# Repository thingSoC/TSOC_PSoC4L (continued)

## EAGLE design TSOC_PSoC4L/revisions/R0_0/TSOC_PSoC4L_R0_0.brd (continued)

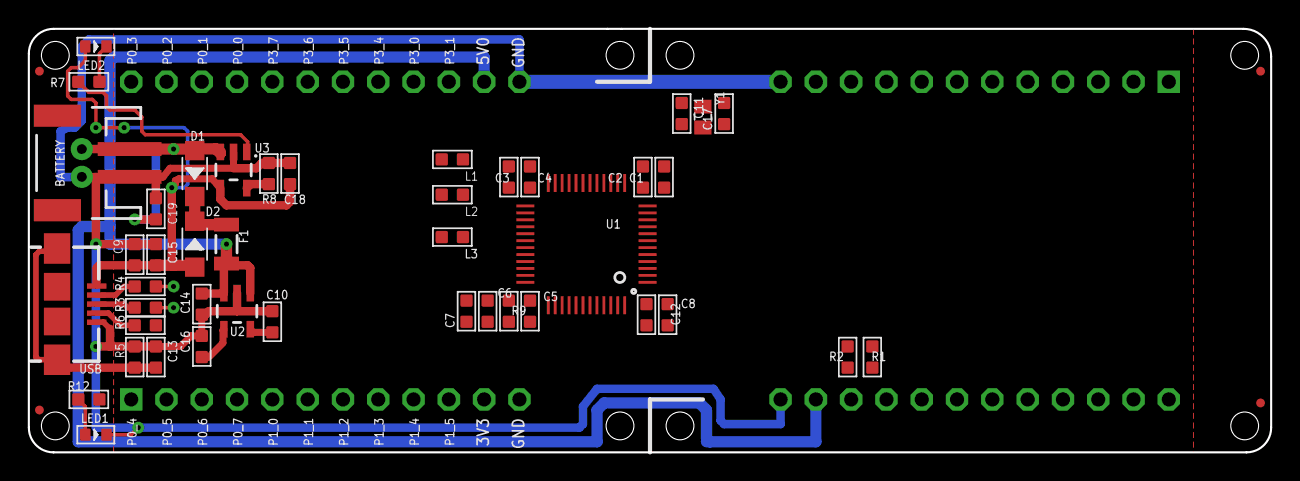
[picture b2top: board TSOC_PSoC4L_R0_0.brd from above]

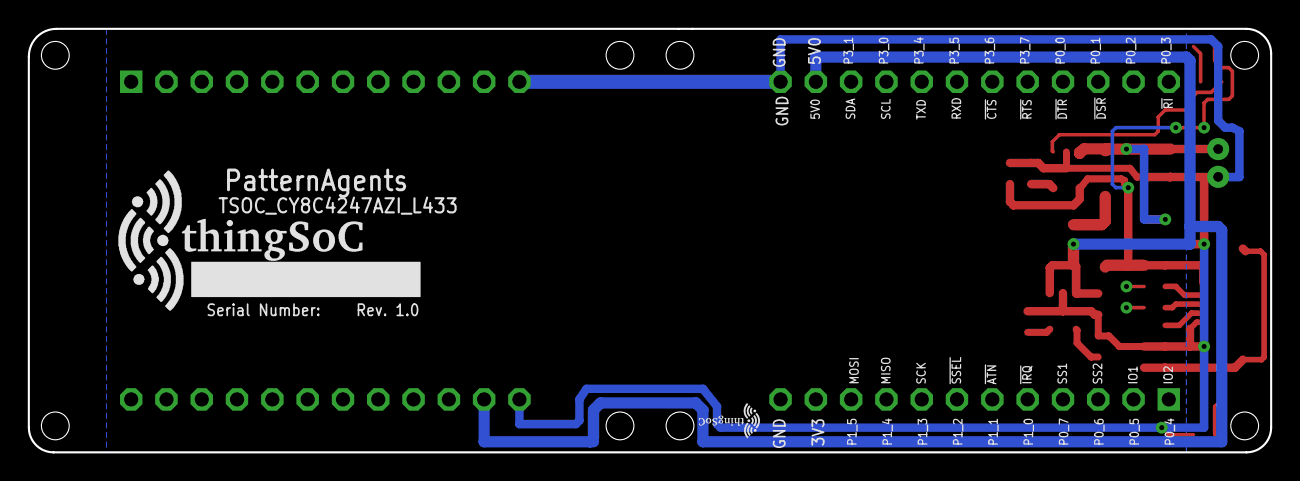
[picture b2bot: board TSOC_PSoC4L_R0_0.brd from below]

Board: 2 copper layers, 89.4 x 30.5 mm, 53 parts (3 on the bottom side), 44 nets.

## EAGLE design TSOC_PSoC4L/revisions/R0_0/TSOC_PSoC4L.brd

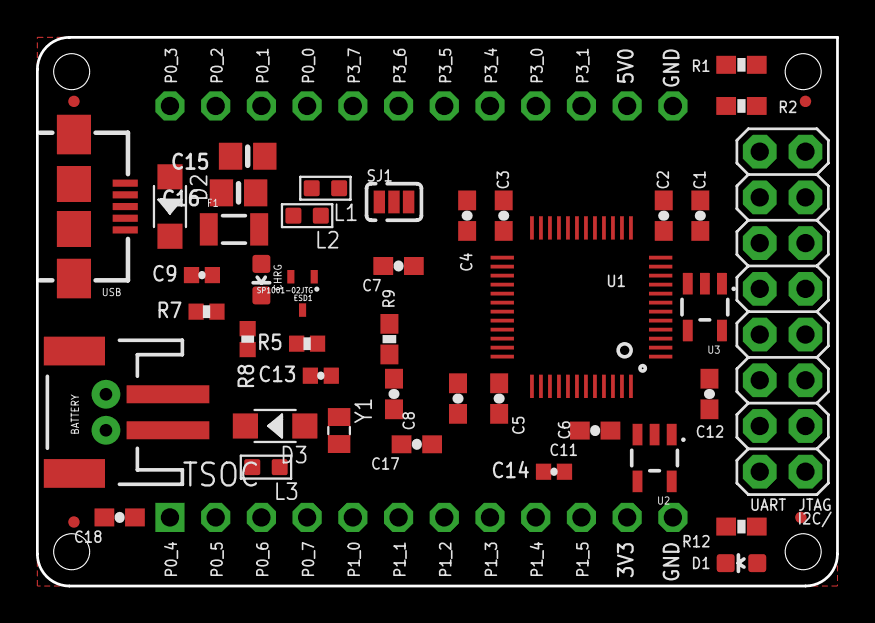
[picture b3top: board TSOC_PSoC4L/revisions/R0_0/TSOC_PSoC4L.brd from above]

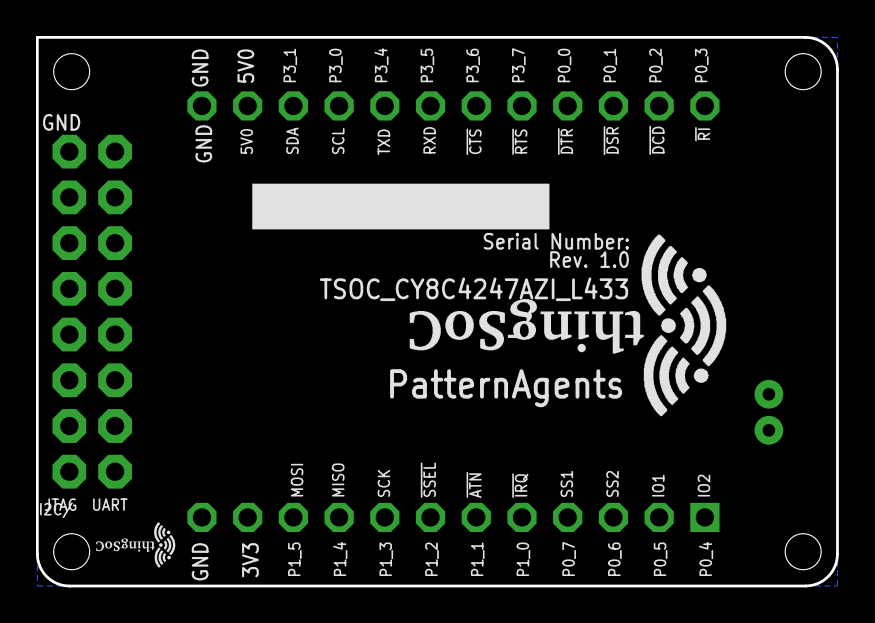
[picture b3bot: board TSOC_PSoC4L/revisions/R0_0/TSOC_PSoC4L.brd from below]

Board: 2 copper layers, 44.5 x 30.5 mm, 50 parts (3 on the bottom side), 51 nets, no tracks yet.

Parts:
BATTERY: JST-2-SMD
C1, C4, C5, C7: 0.1uF; 0603-CAP
C2, C3, C6, C8, C12, C18: 1uF; 0603-CAP
C9: 0.1uF; 0402-CAP
C11, C17: 12pF; 0603-CAP
C13, C14: 470nF; 0402-CAP
C15, C16: 10µF; 0805-NO
CHRG: RED; LED-0603
D1: LED-0603
D2, D3: 20V-1A; SOD-123
ESD1: SP1001-02JTG; SC70-3
F1: 500mA-PTC; PTC-1206
FID1, FID2, FID3, FID4: FIDUCIALUFIDUCIAL; MICRO-FIDUCIAL
J1: 2X8
J1P: JST-2-PTH-NS
L1, L2, L3: 330OHM-500MA; L0603
R1, R2: 2K2; 0603-RES
R5: 1M; 0402-RES
R7: 1K; 0402-RES
R8: 10K; 0402-RES
R9: 10K; 0603-RES
R12: 1K; 0603-RES
SJ1: JMP-3-NC
TSOC: TSOC-24-BB; TSOC-BB-S24
U1: CY8C4247AZI-L433; TQFP-7X7-48
U2: MIC5219 3.3V; SOT23-5
U3: MCP73831; SOT23-5
U$1: TSOC-PCB-SINGLE; TSOC-BB-BRD-DIM
U$100: TSOC-LOGO-SMALL; TSOC-LOGO-SML
U$101: TSOC-LOGO-LRG
USB: USB_AB; USB-AB-MICRO-SMD
Y1: 3.2768KHZ; X2-SMD-L2.0X1.2X0.55MM

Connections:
3V3: C15.1, SJ1.1, TSOC.11B, U2.5
5V0: C16.1, D2.-, D3.-, L2.1, L3.1, SJ1.3, TSOC.11C, U2.1, U2.3
!XRES: C7.1, J1.5, R9.1, U1.36
BYPASS1: C14.1, U2.4
CLED: CHRG.C, R7.2
CSTAT: R7.1, U3.1
GND: BATTERY.1, C1.2, C2.2, C3.2, C4.2, C5.2, C6.2, C7.2, C8.2, C9.2, C11.2, C12.2, C13.2, C14.2, C15.2, C16.2, C17.2, C18.2, D1.C, ESD1.3, J1.15, J1.16, J1P.2, R5.2, R8.1, TSOC.12B, TSOC.12C, U1.10, U1.38, U1.41, U2.2, U3.2, USB.GND
unnamed: R8.2, U3.5
unnamed: D1.A, R12.1
P0_0: TSOC.4C, U1.28
P0_1: TSOC.3C, U1.29
P0_2: TSOC.2C, U1.30
P0_3: TSOC.1C, U1.31
P0_4: C11.1, TSOC.1B, U1.32, Y1.1
P0_5: C17.1, TSOC.2B, U1.33, Y1.2
P0_6: TSOC.3B, U1.34
P0_7: TSOC.4B, U1.35
P1_0: TSOC.5B, U1.42
P1_1: TSOC.6B, U1.43
P1_2: TSOC.7B, U1.44
P1_3: TSOC.8B, U1.45
P1_4: TSOC.9B, U1.46
P1_5: TSOC.10B, U1.47
P1_6: R12.2, U1.48
P1_7: C12.1, U1.1
P2_0: J1.1, U1.2
P2_2: J1.2, U1.4
P2_3: J1.4, U1.5
P2_4: J1.6, U1.6
P2_7: J1.14, U1.9
P3_0: J1.3, R2.1, TSOC.9C, U1.12
P3_1: J1.13, R1.1, TSOC.10C, U1.13
P3_2: J1.9, U1.14
P3_3: J1.7, U1.16
P3_4: TSOC.8C, U1.17
P3_5: TSOC.7C, U1.18
P3_6: TSOC.6C, U1.19
P3_7: TSOC.5C, U1.20
P4_0: J1.10, U1.22
SJ1: L1.1, SJ1.2
USB1_DM: ESD1.2, U1.24, USB.D-
USB1_DP: ESD1.1, U1.23, USB.D+
USB1_SHIELD: C13.1, R5.1, USB.SHIELD1, USB.SHIELD2
USB1_VBUS: C18.1, CHRG.A, D2.+, F1.2, U1.25, U3.4
VBAT: BATTERY.2, D3.+, J1P.1, U3.3
VBUS1: C9.1, F1.1, USB.VBUS
VCC: J1.11, J1.12
VCCD: C8.1, U1.37
VDDA: C1.1, C2.1, L3.2, U1.40
VDDD: C5.1, C6.1, L2.2, R9.2, U1.39
VDDIO: C3.1, C4.1, L1.2, R1.2, R2.2, U1.21

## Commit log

2016-11-06 update PSoC4L
2016-11-13 sync/update
2016-11-18 update hardware files
2017-01-14 update documetation
2017-02-28 update docs
